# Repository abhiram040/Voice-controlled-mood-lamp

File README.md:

# Voice-controlled-mood-lamp
It is a mood lamp made with rgb led where the colour of the lamp can be changed by voice command.The project uses 8-bit Atmega 328 microcontroller.the voice command is given from mobile app which communicates with microcontroller using Hc05 bluetooth module.

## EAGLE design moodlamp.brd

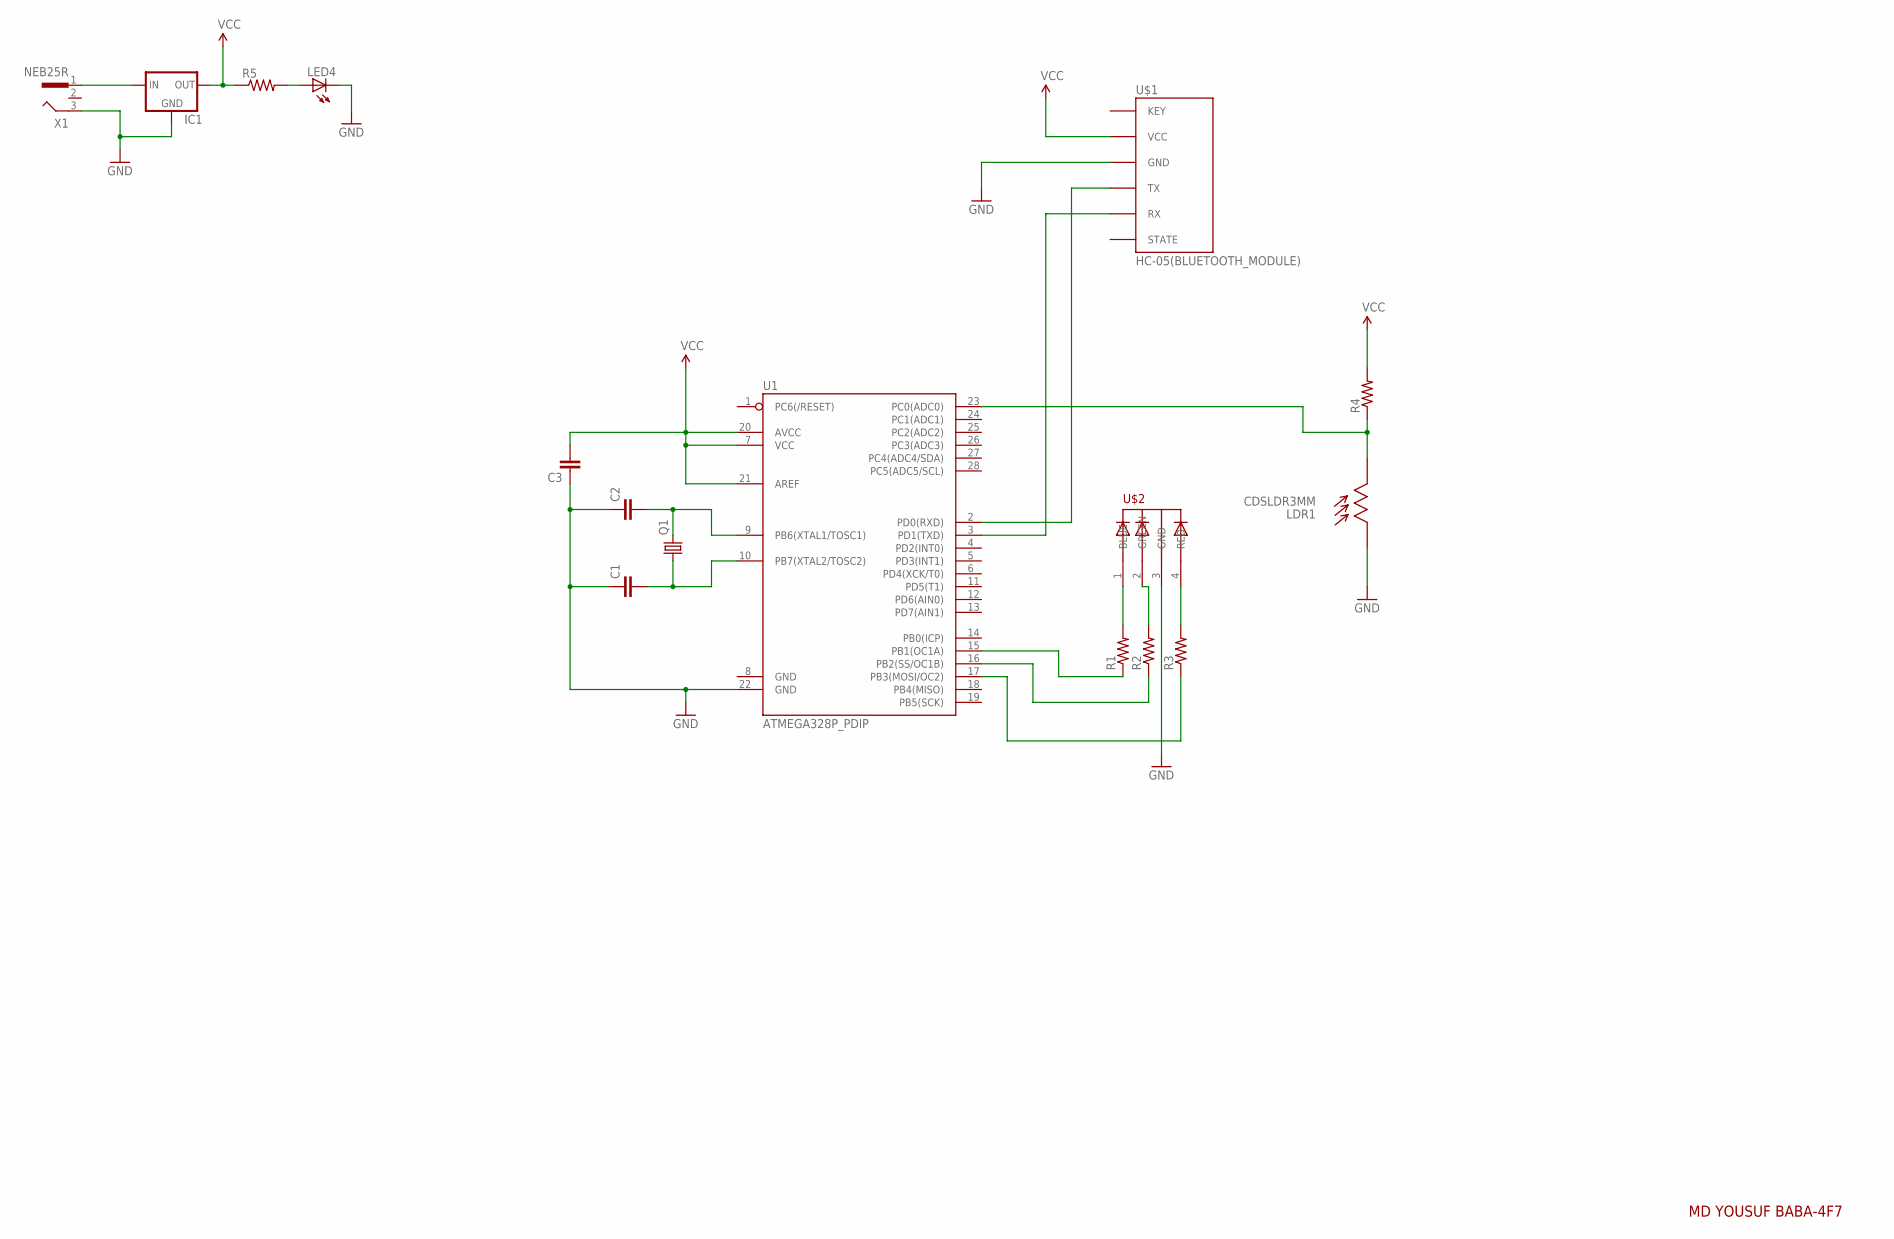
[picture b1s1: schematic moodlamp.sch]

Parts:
C1, C2, C3: C-EU025-024X044; C025-024X044
IC1: V_REG_78XX-TO-220; TO-220-ALT
LDR1: CDSLDR3MM; LDR3MM
LED4: LED3MM
Q1: CRYSTALHC49US; HC49US
R1, R2, R3, R4, R5: RESISTOR0207/7; 0207/7
U1: ATMEGA328P_PDIP; DIL28-3
U$1: HC-05(BLUETOOTH_MODULE); HC-05
U$2: 5MMRGBLED; LED5MMRGB
X1: NEB25R

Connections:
GND: C1.1, C2.1, C3.1, IC1.GND, LDR1.P$1, LED4.K (C), U1.22 (GND), U$1.GND, U$2.3 (GND), X1.3
unnamed: R1.1, U1.15 (PB1(OC1A))
unnamed: R2.1, U1.16 (PB2(SS/OC1B))
unnamed: R3.1, U1.17 (PB3(MOSI/OC2))
unnamed: R1.2, U$2.1 (BLUE)
unnamed: R2.2, U$2.2 (GREEN)
unnamed: R3.2, U$2.4 (RED)
unnamed: LDR1.P$2, R4.1, U1.23 (PC0(ADC0))
unnamed: C2.2, Q1.2, U1.9 (PB6(XTAL1/TOSC1))
unnamed: LED4.A, R5.2
unnamed: IC1.IN, X1.1
unnamed: C1.2, Q1.1, U1.10 (PB7(XTAL2/TOSC2))
unnamed: U1.2 (PD0(RXD)), U$1.TX
unnamed: U1.3 (PD1(TXD)), U$1.RX
VCC: C3.2, IC1.OUT, R4.2, R5.1, U1.7 (VCC), U1.20 (AVCC), U1.21 (AREF), U$1.VCC

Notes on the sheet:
MD YOUSUF BABA-4F7

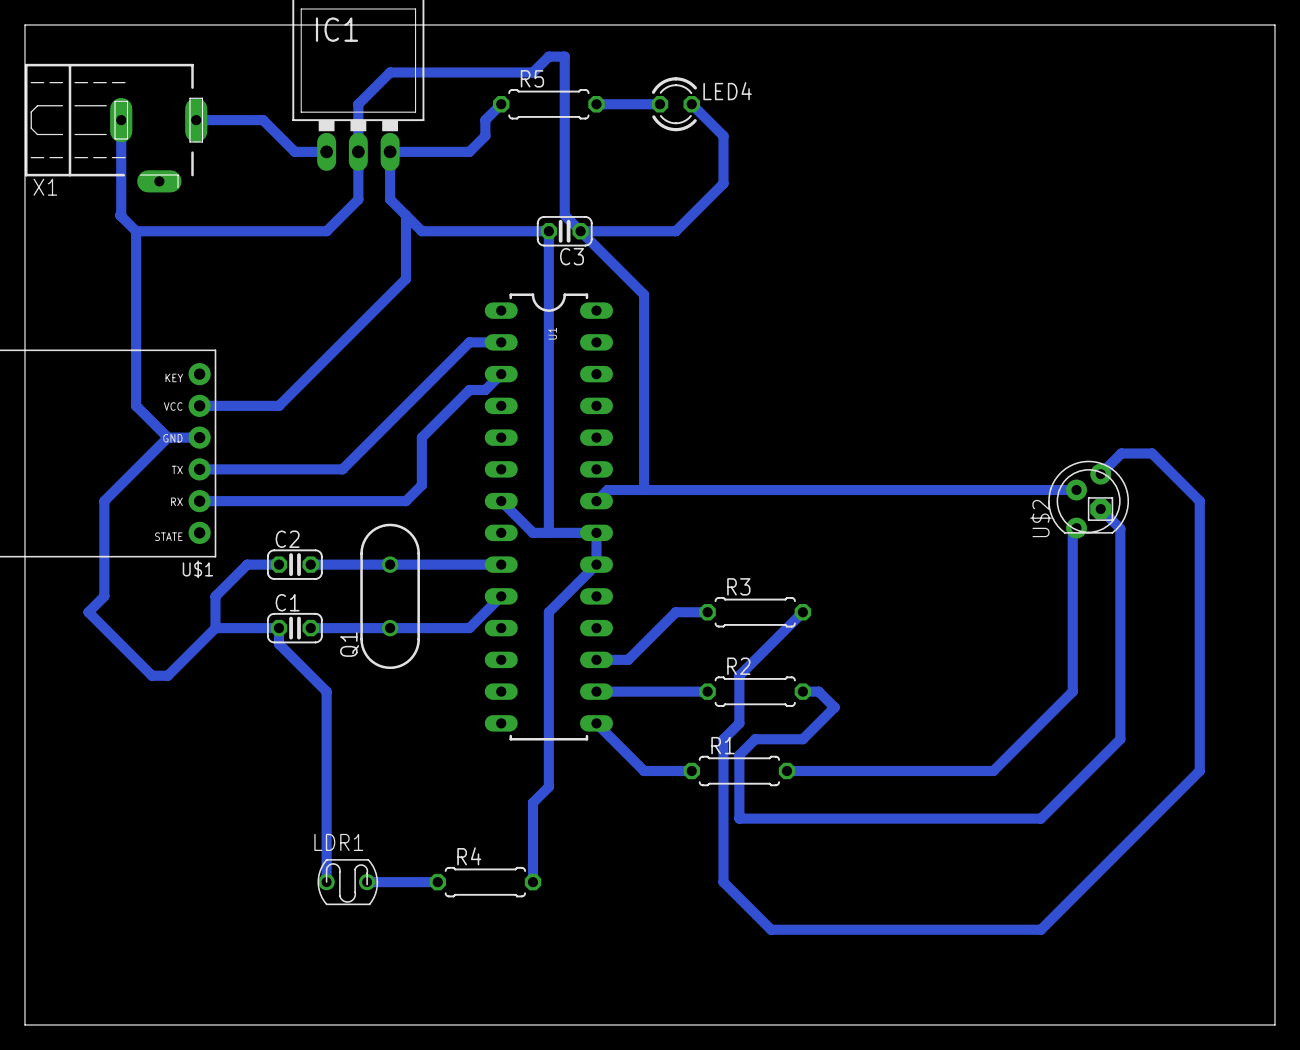
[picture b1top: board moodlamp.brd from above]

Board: 2 copper layers, 100.0 x 80.0 mm, 16 parts (0 on the bottom side), 15 nets.

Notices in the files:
parts and their libraries:
SparkFun-PowerIC: Licensing: Creative Commons ShareAlike 4.0 International - https://creativecommons.org/licenses/by-sa/4.0
